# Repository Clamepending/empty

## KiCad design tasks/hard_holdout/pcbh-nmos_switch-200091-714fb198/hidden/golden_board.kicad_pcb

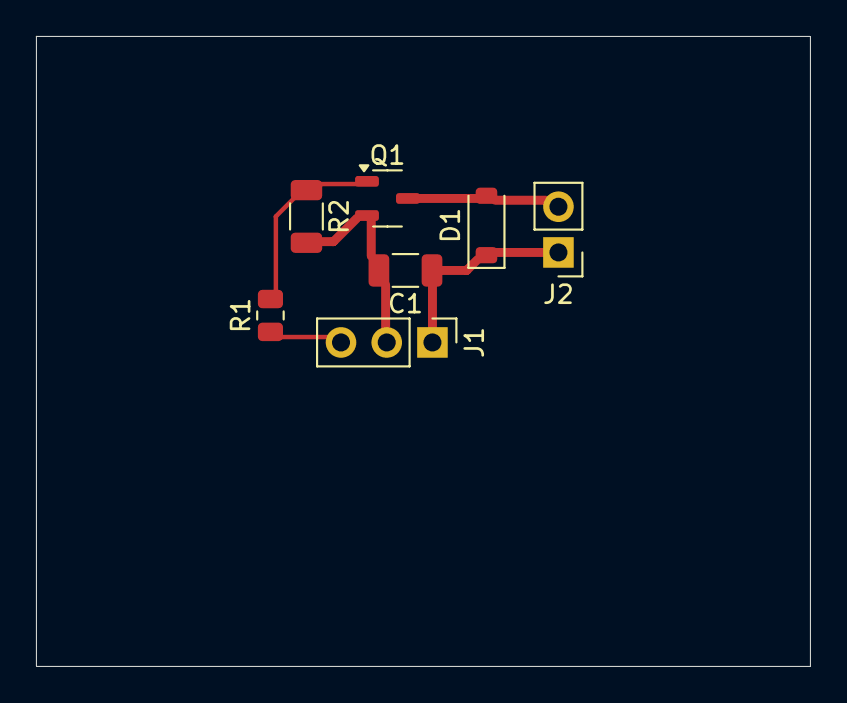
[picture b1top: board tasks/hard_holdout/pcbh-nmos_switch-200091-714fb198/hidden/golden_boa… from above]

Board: 2 copper layers, 43.0 x 35.0 mm, 7 parts (0 on the bottom side), 5 nets.

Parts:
C1: 1.5u; C_1206_3216Metric
D1: D_SOD-123
J1: PinHeader_1x03_P2.54mm_Vertical
J2: PinHeader_1x02_P2.54mm_Vertical
Q1: SOT-23-3
R1: 100; R_0805_2012Metric
R2: 12k; R_1206_3216Metric

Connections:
+9V: C1.1, D1.1, J1.1, J2.1
CTRL: J1.3, R1.1
GATE: Q1.1, R1.2, R2.1
GND: C1.2, J1.2, Q1.2, R2.2
SW: D1.2, J2.2, Q1.3

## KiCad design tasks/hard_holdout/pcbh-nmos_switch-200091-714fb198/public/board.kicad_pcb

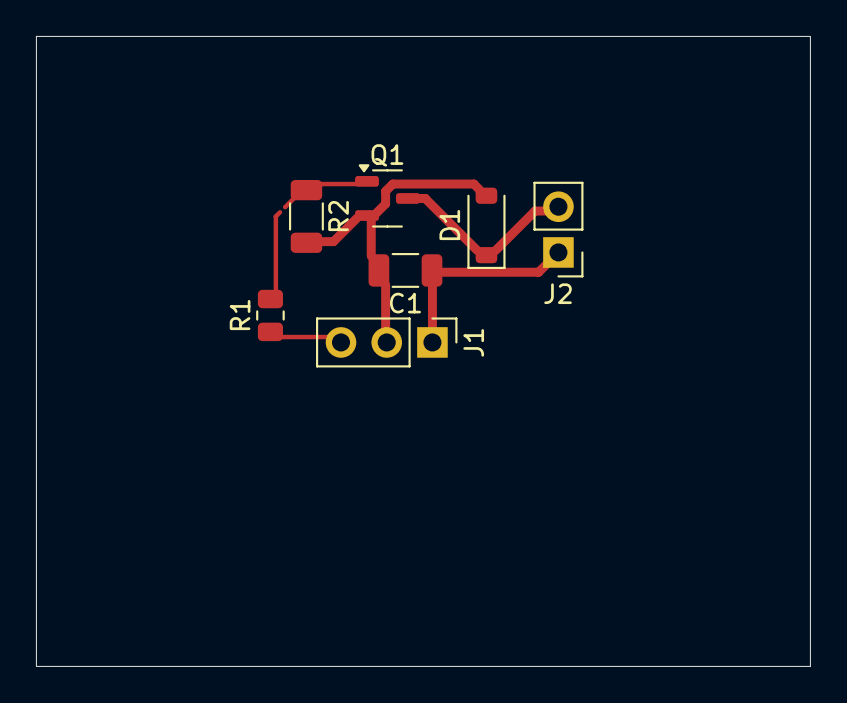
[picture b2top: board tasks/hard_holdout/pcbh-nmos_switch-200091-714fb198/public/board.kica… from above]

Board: 2 copper layers, 43.0 x 35.0 mm, 7 parts (0 on the bottom side), 5 nets.

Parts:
C1: 1.5u; C_1206_3216Metric
D1: D_SOD-123
J1: PinHeader_1x03_P2.54mm_Vertical
J2: PinHeader_1x02_P2.54mm_Vertical
Q1: SOT-23-3
R1: 100; R_0805_2012Metric
R2: 12k; R_1206_3216Metric

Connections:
+9V: C1.1, J1.1, J2.1
CTRL: J1.3, R1.1
GATE: Q1.1, R1.2, R2.1
GND: C1.2, D1.2, J1.2, Q1.2, R2.2
SW: D1.1, J2.2, Q1.3

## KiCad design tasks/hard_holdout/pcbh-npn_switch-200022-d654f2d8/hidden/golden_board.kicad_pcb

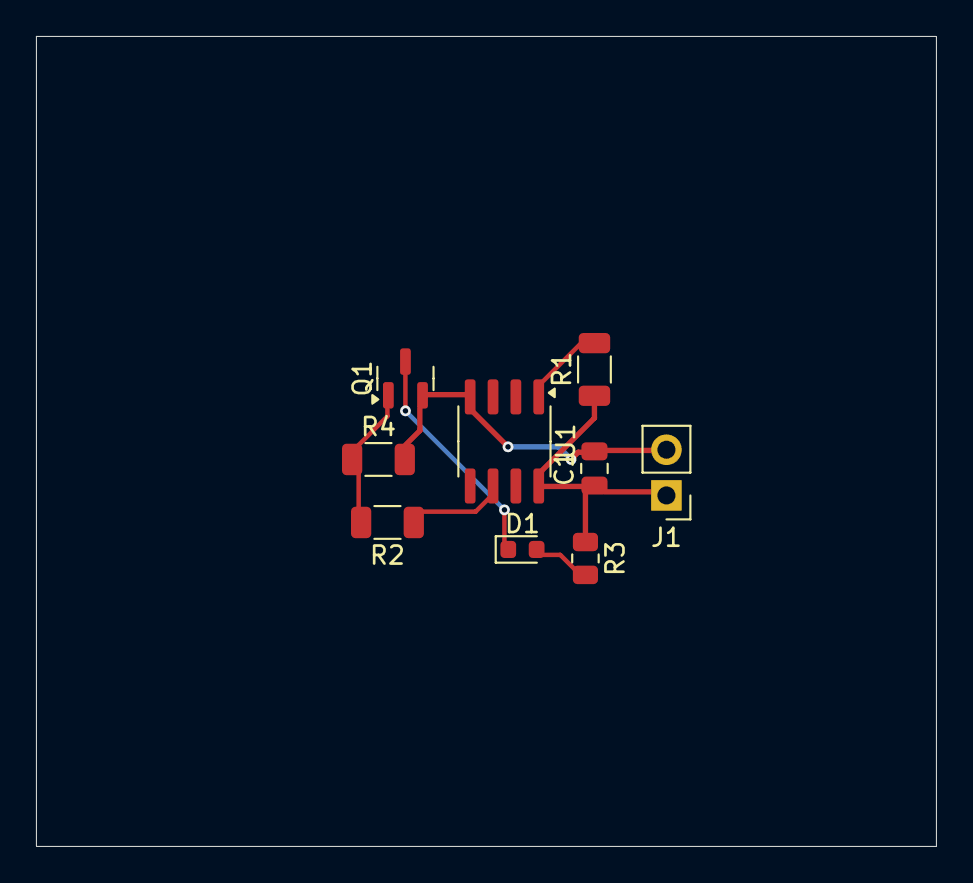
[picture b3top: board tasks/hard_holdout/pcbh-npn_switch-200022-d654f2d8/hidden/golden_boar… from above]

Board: 2 copper layers, 50.0 x 45.0 mm, 9 parts (0 on the bottom side), 7 nets.

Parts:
C1: 1u; C_0805_2012Metric
D1: LED_0603_1608Metric
J1: PinHeader_1x02_P2.54mm_Vertical
Q1: SOT-23
R1: 33k; R_1206_3216Metric
R2: 2.7k; R_1206_3216Metric
R3: 180; R_0805_2012Metric
R4: 11k; R_1206_3216Metric
U1: SOIC-8_3.9x4.9mm_P1.27mm

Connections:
+5V: C1.1, J1.1, R1.1, R3.1, U1.8
BASE: Q1.1, R2.2, R4.1
CTRL: R2.1, U1.6
GND: C1.2, J1.2, Q1.2, R4.2, U1.4
LED_A: D1.2, R3.2
NRST: R1.2, U1.1
SW: D1.1, Q1.3

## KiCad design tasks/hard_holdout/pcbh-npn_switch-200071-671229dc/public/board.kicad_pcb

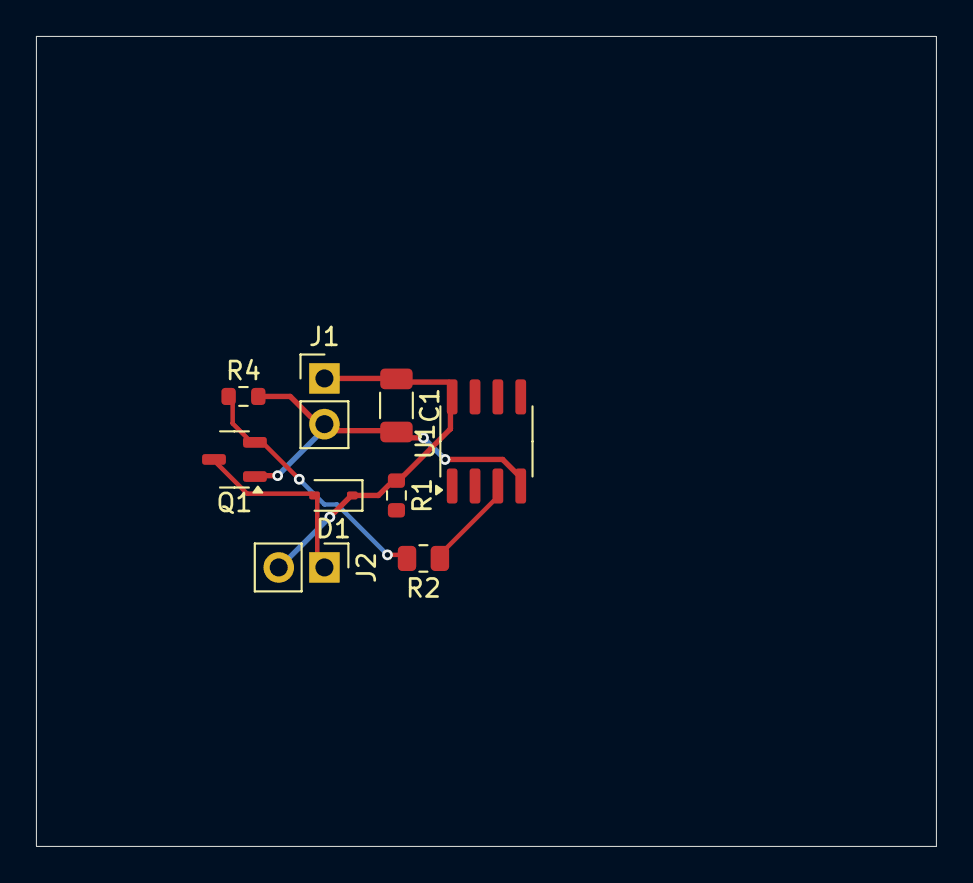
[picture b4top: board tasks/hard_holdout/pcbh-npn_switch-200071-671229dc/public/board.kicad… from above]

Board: 2 copper layers, 50.0 x 45.0 mm, 9 parts (0 on the bottom side), 5 nets.

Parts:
C1: 100n; C_1206_3216Metric
D1: D_SOD-323
J1, J2: PinHeader_1x02_P2.54mm_Vertical
Q1: SOT-23-3
R1: 6.8k; R_0603_1608Metric
R2: 1.2k; R_0805_2012Metric
R4: 20k; R_0603_1608Metric
U1: SOIC-8_3.9x4.9mm_P1.27mm

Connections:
+5V: C1.1, D1.1, J1.1, J2.2, R1.1, U1.8
BASE: Q1.2, R2.2, R4.1
CTRL: R2.1, U1.3
GND: C1.2, J1.2, Q1.1, R4.2, U1.4
SW: D1.2, J2.1, Q1.3
